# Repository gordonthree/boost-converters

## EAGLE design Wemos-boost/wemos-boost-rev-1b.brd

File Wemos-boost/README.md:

# High voltage boost converter with room for a WeMos D1 mini for wireless control

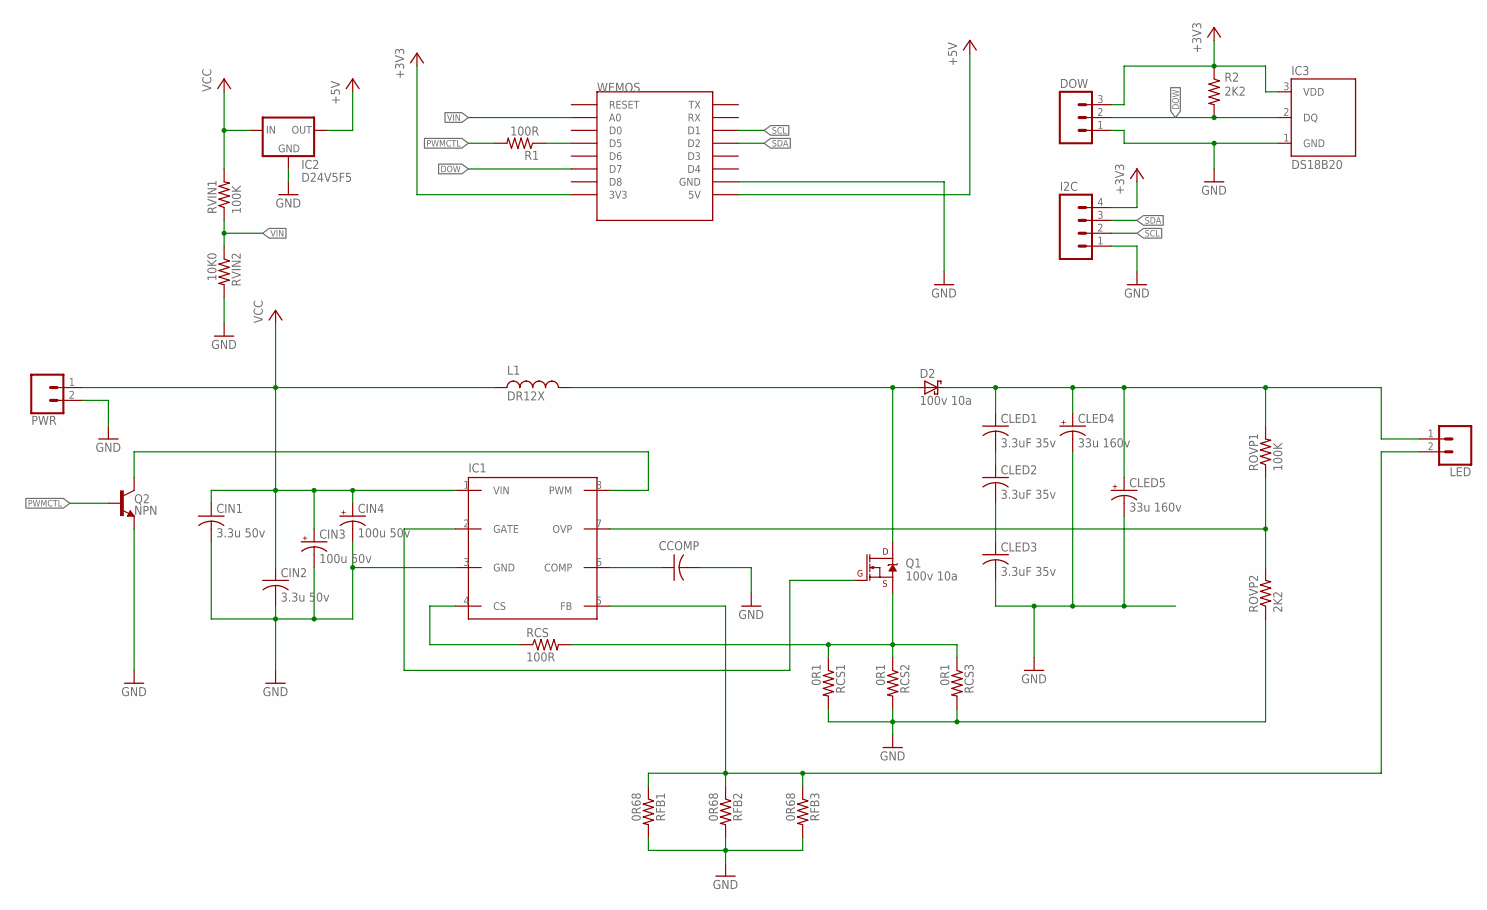
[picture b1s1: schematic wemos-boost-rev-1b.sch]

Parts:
CCOMP: C-USC0603; C0603
CIN1, CIN2: 3.3u 50v; C1210
CIN3, CIN4: 100u 50v; PANASONIC_F
CLED1, CLED2, CLED3: 3.3uF 35v; C0805
CLED4, CLED5: 33u 160v; PANASONIC_G
D2: 100v 10a; SMB
DOW: M03SCREW_LOCK; SCREWTERMINAL-3.5MM-3_LOCK.007S
I2C: M04SCREW_LOCK; SCREWTERMINAL-3.5MM-4_LOCK
IC1: AL8853S-13; SOP08
IC2: D24V5F5; 78XXS
IC3: DS18B20; TO-92-AMMO
L1: DR12X
LED: CONN_025MM; SCREWTERMINAL-5MM-2
PWR: CONN_025MM; SCREWTERMINAL-5MM-2
Q1: 100v 10a; TO-252/DPAK
Q2: NPN; SOT23-3
R1: 100R; R0603
R2: 2K2; R0603
RCS: 100R; R0603
RCS1, RCS2, RCS3: 0R1; R2010
RFB1, RFB2, RFB3: 0R68; R1206
ROVP1: 100K; R0603
ROVP2: 2K2; R0603
RVIN1: 100K; R0603
RVIN2: 10K0; R0603
WEMOS: WEMOS-D1-MINI

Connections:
+3V3: DOW.3, I2C.4, IC3.3 (VDD), R2.1, WEMOS.3V3
+5V: IC2.OUT, WEMOS.5V
COMP: CCOMP.1, IC1.6 (COMP)
CS: IC1.4 (CS), RCS.1
CS`: Q1.3 (S), RCS.2, RCS1.1, RCS2.1, RCS3.1
DOW: DOW.2, IC3.2 (DQ), R2.2, WEMOS.D7
FB: IC1.5 (FB), LED.2, RFB1.1, RFB2.1, RFB3.1
GATE: IC1.2 (GATE), Q1.1 (G)
GND: CCOMP.2, CIN1.2, CIN2.2, CIN3.-, CIN4.-, CLED3.2, CLED4.-, CLED5.-, DOW.1, I2C.1, IC1.3 (GND), IC2.GND, IC3.1 (GND), PWR.2, Q2.2 (E), RCS1.2, RCS2.2, RCS3.2, RFB1.2, RFB2.2, RFB3.2, ROVP2.1, RVIN2.2, WEMOS.GND
LEDPWR: CLED1.1, CLED4.+, CLED5.+, D2.K, LED.1, ROVP1.2
unnamed: R1.1, WEMOS.D5
unnamed: CLED1.2, CLED2.1
unnamed: CLED2.2, CLED3.1
OVP: IC1.7 (OVP), ROVP1.1, ROVP2.2
PWM: IC1.8 (PWM), Q2.3 (C)
PWMCTL: Q2.1 (B), R1.2
SCL: I2C.2, WEMOS.D1
SDA: I2C.3, WEMOS.D2
SWITCHNODE: D2.A, L1.P$1, Q1.2 (D)
VCC: CIN1.1, CIN2.1, CIN3.+, CIN4.+, IC1.1 (VIN), IC2.IN, L1.P$2, PWR.1, RVIN1.2
VIN: RVIN1.1, RVIN2.1, WEMOS.A0

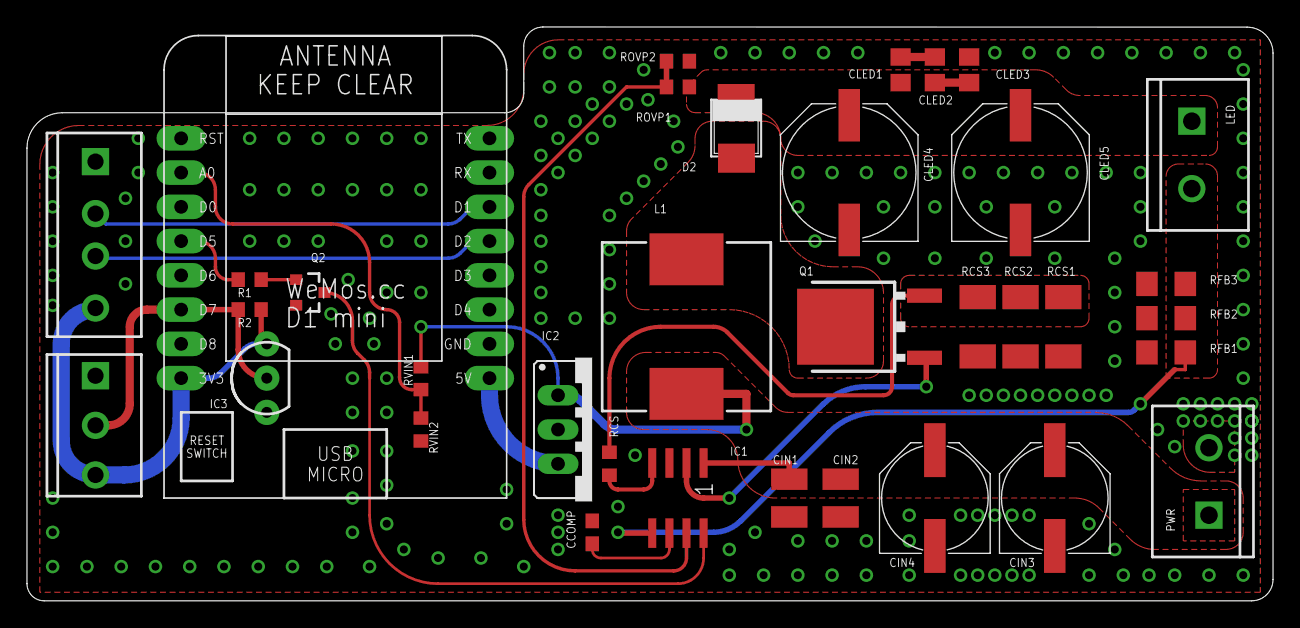
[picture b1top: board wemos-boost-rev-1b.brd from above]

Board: 2 copper layers, 92.4 x 42.5 mm, 35 parts (0 on the bottom side), 21 nets.

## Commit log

2022-08-30 Added Wemos-Boost
2022-08-30 added README
2022-08-30 added gitignore

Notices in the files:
parts and their libraries:
SparkFun-DiscreteSemi: Licensing: Creative Commons ShareAlike 4.0 International - https://creativecommons.org/licenses/by-sa/4.0
